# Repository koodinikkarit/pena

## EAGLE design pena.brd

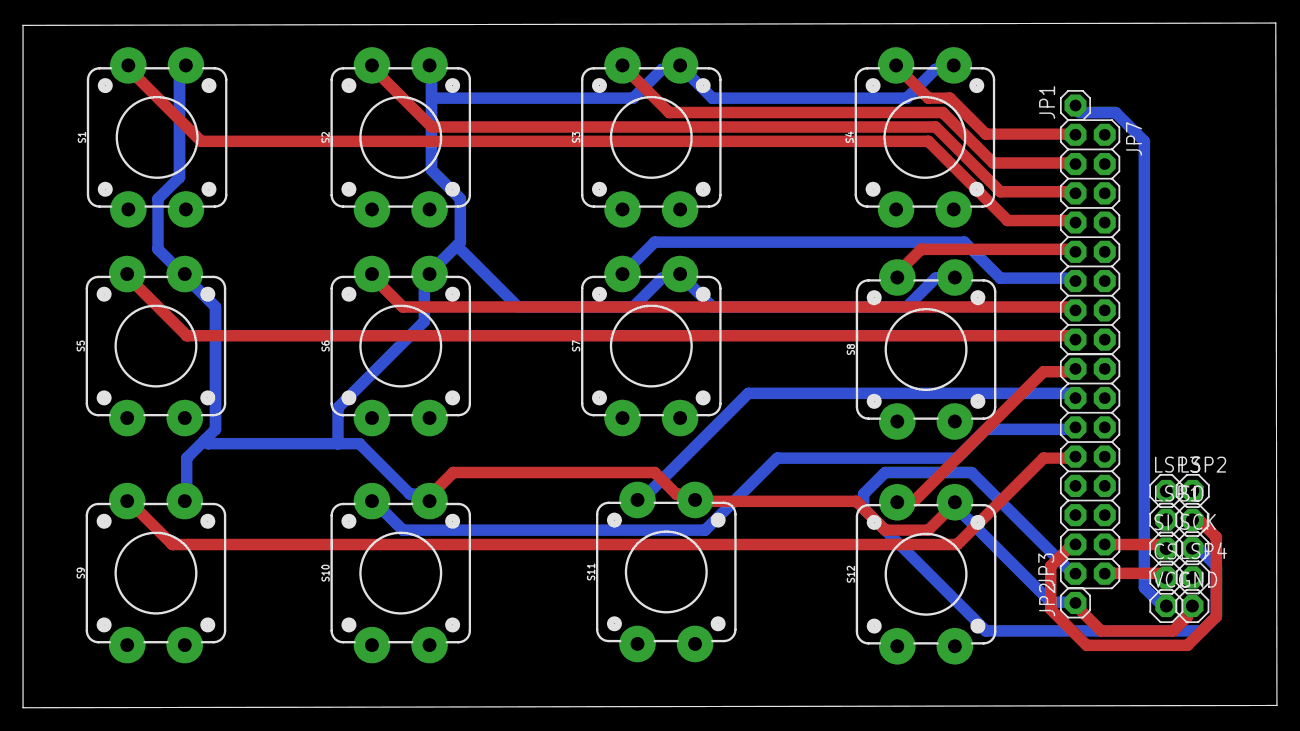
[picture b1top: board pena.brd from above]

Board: 2 copper layers, 108.9 x 59.4 mm, 26 parts (0 on the bottom side), 18 nets.

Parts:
CS: SE11
GND: SE11
JP1, JP2: 1X01
JP3, JP7: 2X08
LSP1, LSP2, LSP3, LSP4: SE11
S1, S2, S3, S4, S5, S6, S7, S8, S9, S10, S11, S12: TACTILE_SWITCH_PTH_12MM
SCK: SE11
SI: SE11
SO: SE11
VCC: SE11

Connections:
22: JP7.1, S4.3
24: JP7.3, S3.3
26: JP7.5, S2.3
28: JP7.7, S1.3
30: JP7.9, S8.3
32: JP7.11, S7.3
34: JP7.13, S6.3
36: JP7.15, S5.3
38: JP3.16, S12.3
40: JP3.14, S11.3
42: JP3.12, S10.3
44: JP3.10, S9.3
50: JP3.4, SO.MP
51: JP3.3, SI.MP
52: JP3.2, SCK.MP
53: CS.MP, JP3.1
+5V: JP1.1, VCC.MP
GND: GND.MP, JP2.1, S1.1, S2.1, S3.1, S4.1, S5.1, S6.1, S7.1, S8.1, S9.1, S10.1, S11.1, S12.1

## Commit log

2017-02-01 Luotu peruspena.
2017-02-01 Vaihdettu boardin kokoa.
2017-02-07 Muutettu boardin kokoa, reikien kokoa sekä poistettu alasveto vastukset.
2017-02-07 Lisätty pdf uusista kaavioista.
2017-02-07 Muutettu boardin kokoa sekä jarjestelty nappeja.
2017-02-08 Vaihdettu reiän kokoa
2017-02-08 Muutettu reikien kokoa sekä siirretty niitä.
2017-02-08 Vaihettu reikien kokoa.
2017-02-08 Vaihdettu reikien kokoa.
2017-02-08 Luotu routet.
2017-02-08 Lisätty pdf kaavioista.
2017-04-19 Järjestelty scheman komponentteja.

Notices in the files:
parts and their libraries:
SparkFun-Switches: Licensing: Creative Commons ShareAlike 4.0 International - https://creativecommons.org/licenses/by-sa/4.0
